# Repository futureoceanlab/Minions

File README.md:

# Minions
This repository contains software and hardware assets for the Minions 
stereo imaging system project. The design and evaluation based on these
assets are thoroughly described in 
<a href="https://www.dropbox.com/s/i847r4oa8v05839/junsuj-ms-2020.pdf?dl=0">Junsu's thesis</a>.

## Circuit
This directory contains the circuit related assets: schematic, board layout 
and the gerber file. They were used to develop and evaluate the necessary
components to communicate and control peripheral electronics of the 
Minion stereo camera components. EAGLE software is required.

## Code
The software components of the project can be broken down into four major
parts:
- **PTV**: We devised a simulation of the settling marine snow. We also 
apply PTV to track those particles and evaluated the performance of the PTV. 
- **Firmware**: Firmware to control cameras and LED during deployment.
- **Optical Simulation**: Simulation tools to evaluate the designs of the stereo
optical system.
- **Optical Analysis**: Analysis of empirical measurements of the imaging 
system and the lighting systems.

More detailed explanations of the code can be found in each of the sub-directories
and in the code itself.

## Mechanical
The mechanical component of the project remains to be done. The assets will
be added as the project progresses.

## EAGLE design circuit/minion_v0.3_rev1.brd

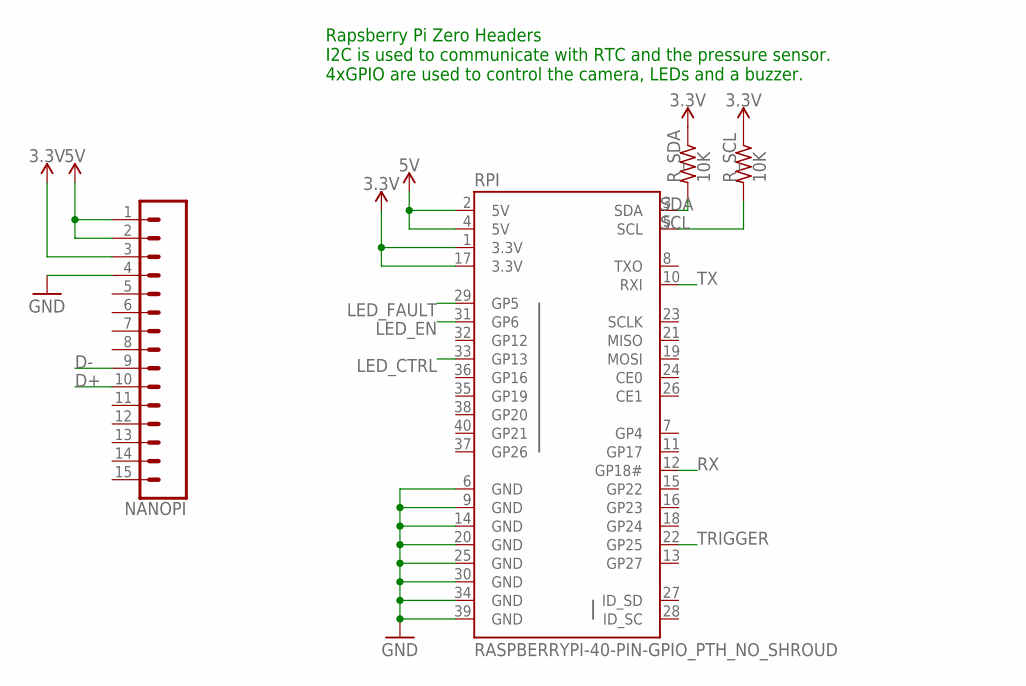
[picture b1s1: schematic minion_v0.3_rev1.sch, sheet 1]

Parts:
NANOPI: CONN_15; 1X15
RPI: RASPBERRYPI-40-PIN-GPIO_PTH_NO_SHROUD; 2X20
R_SCL: 10K; RES_0603
R_SDA: 10K; RES_0603

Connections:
3.3V: NANOPI.3, RPI.1 (3.3V), RPI.17 (3.3V), R_SCL.1, R_SDA.1; also elsewhere on the board
5V: NANOPI.1, NANOPI.2, RPI.2 (5V), RPI.4 (5V); also elsewhere on the board
D+: NANOPI.10; also elsewhere on the board
D-: NANOPI.9; also elsewhere on the board
GND: NANOPI.4, RPI.6 (GND), RPI.9 (GND), RPI.14 (GND), RPI.20 (GND), RPI.25 (GND), RPI.30 (GND), RPI.34 (GND), RPI.39 (GND); also elsewhere on the board
LED_CTRL: RPI.33 (GP13); also elsewhere on the board
LED_EN: RPI.31 (GP6); also elsewhere on the board
LED_FAULT: RPI.29 (GP5); also elsewhere on the board
RX: RPI.12 (GP18#); also elsewhere on the board
SCL: RPI.5 (SCL), R_SCL.2; also elsewhere on the board
SDA: RPI.3 (SDA), R_SDA.2; also elsewhere on the board
TRIGGER: RPI.22 (GP25); also elsewhere on the board
TX: RPI.10 (RXI); also elsewhere on the board

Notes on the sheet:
Rapsberry Pi Zero Headers I2C is used to communicate with RTC and the pressure sensor. 4xGPIO are used to control the camera, LEDs and a buzzer.

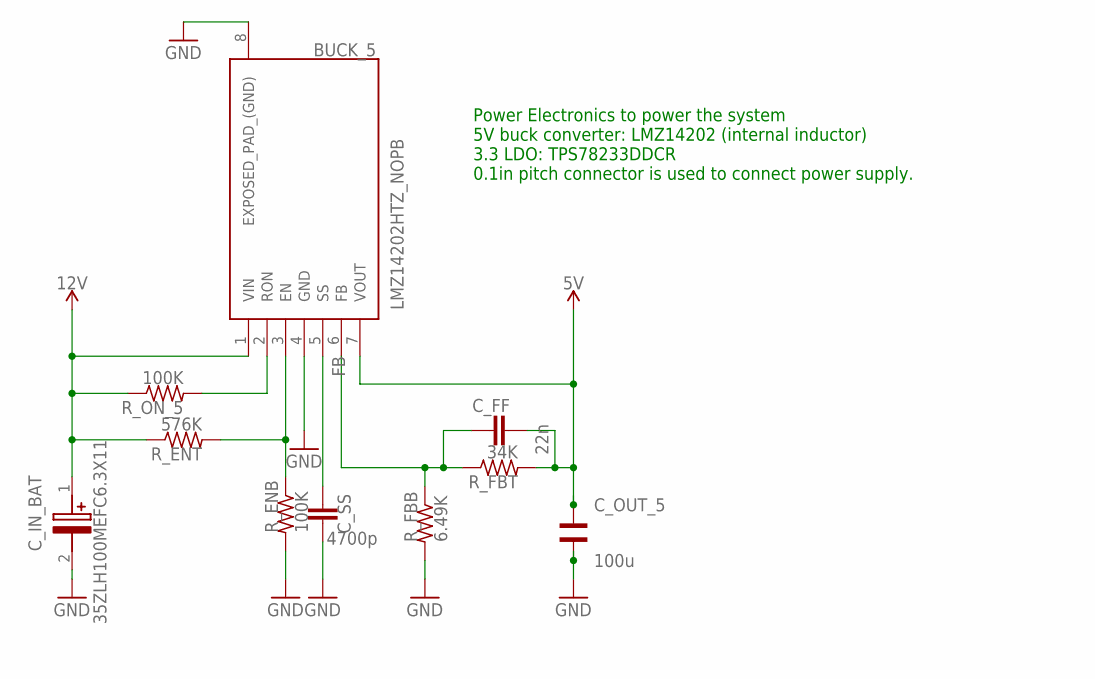
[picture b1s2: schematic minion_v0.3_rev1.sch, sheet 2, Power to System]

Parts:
BUCK_5: LMZ14202HTZ_NOPB; NDW0007A
C_FF: 22n; CAP_0603
C_IN_BAT: 35ZLH100MEFC6.3X11; CAPPRD250W50D680H1250
C_OUT_5: 100u; WCAP-CSGP_1206
C_SS: 4700p; CAP_0603
R_ENB: 100K; RES_0603
R_ENT: 576K; RES_0603
R_FBB: 6.49K; RES_0603
R_FBT: 34K; RES_0603
R_ON_5: 100K; RES_0603

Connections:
5V: BUCK_5.7 (VOUT), C_FF.2, C_OUT_5.2, R_FBT.2; also elsewhere on the board
12V: BUCK_5.1 (VIN), C_IN_BAT.1 (+), R_ENT.1, R_ON_5.1; also elsewhere on the board
FB: BUCK_5.6 (FB), C_FF.1, R_FBB.1, R_FBT.1
GND: BUCK_5.4 (GND), BUCK_5.8 (EXPOSED_PAD_(GND)), C_IN_BAT.2 (-), C_OUT_5.1, C_SS.2, R_ENB.2, R_FBB.2; also elsewhere on the board
unnamed: BUCK_5.2 (RON), R_ON_5.2
unnamed: BUCK_5.3 (EN), R_ENB.1, R_ENT.2
unnamed: BUCK_5.5 (SS), C_SS.1

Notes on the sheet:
Power Electronics to power the system 5V buck converter: LMZ14202 (internal inductor) 3.3 LDO: TPS78233DDCR 0.1in pitch connector is used to connect power supply.

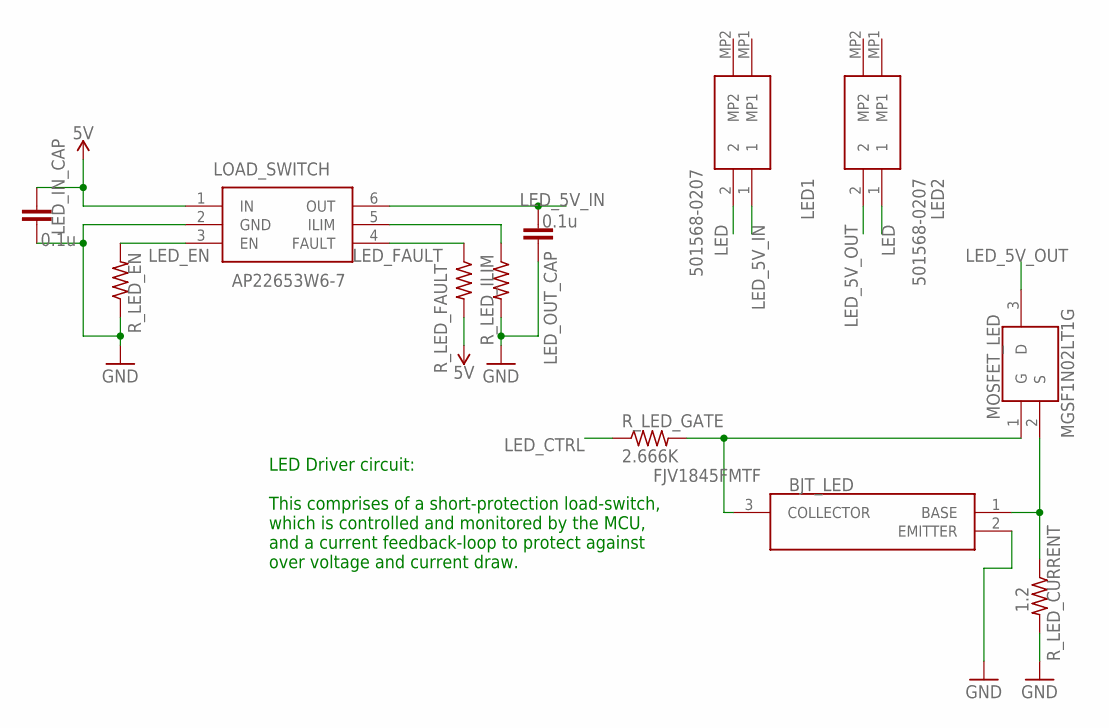
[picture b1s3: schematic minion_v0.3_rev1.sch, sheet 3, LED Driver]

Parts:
BJT_LED: FJV1845FMTF; SOT95P240X114-3N
LED1, LED2: 501568-0207; 5015680207
LED_IN_CAP: 0.1u; CAP_0603
LED_OUT_CAP: 0.1u; CAP_0603
LOAD_SWITCH: AP22653W6-7; SOT95P285X140-6N; MANUFACTURER_PART_NUMBER AP22653; MOUSER_PART_NUMBER 621-AP22653W6-7
MOSFET_LED: MGSF1N02LT1G; SOT96P237X111-3N
R_LED_CURRENT: 1.2; RES_0603
R_LED_EN: 10K; RES_0603
R_LED_FAULT: 10K; RES_0603
R_LED_GATE: 2.666K; RES_0603
R_LED_ILIM: 10K; RES_0603

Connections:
5V: LED_IN_CAP.1, LOAD_SWITCH.1 (IN), R_LED_FAULT.2; also elsewhere on the board
GND: BJT_LED.2 (EMITTER), LED_IN_CAP.2, LED_OUT_CAP.2, LOAD_SWITCH.2 (GND), R_LED_CURRENT.2, R_LED_EN.1, R_LED_ILIM.2; also elsewhere on the board
LED: LED1.2, LED2.1
LED_5V_IN: LED1.1, LED_OUT_CAP.1, LOAD_SWITCH.6 (OUT)
LED_5V_OUT: LED2.2, MOSFET_LED.3 (D)
LED_CTRL: R_LED_GATE.1; also elsewhere on the board
LED_EN: LOAD_SWITCH.3 (EN), R_LED_EN.2; also elsewhere on the board
LED_FAULT: LOAD_SWITCH.4 (FAULT), R_LED_FAULT.1; also elsewhere on the board
unnamed: BJT_LED.3 (COLLECTOR), MOSFET_LED.1 (G), R_LED_GATE.2
unnamed: BJT_LED.1 (BASE), MOSFET_LED.2 (S), R_LED_CURRENT.1
unnamed: LOAD_SWITCH.5 (ILIM), R_LED_ILIM.1

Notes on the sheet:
LED Driver circuit: This comprises of a short-protection load-switch, which is controlled and monitored by the MCU, and a current feedback-loop to protect against over voltage and current draw.

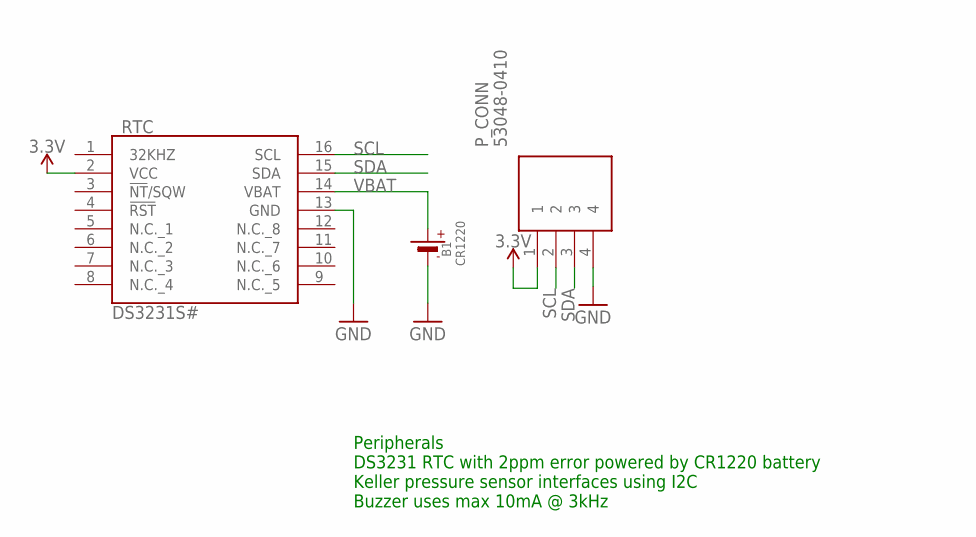
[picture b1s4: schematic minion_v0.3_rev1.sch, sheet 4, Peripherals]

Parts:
B1: CR1220
P_CONN: 53048-0410; SHDR4W35P0X125_1X4_675X550X370
RTC: DS3231S#; SOIC127P1032X265-16N

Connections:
3.3V: P_CONN.1, RTC.2 (VCC); also elsewhere on the board
GND: B1.-, P_CONN.4, RTC.13 (GND); also elsewhere on the board
SCL: P_CONN.2, RTC.16 (SCL); also elsewhere on the board
SDA: P_CONN.3, RTC.15 (SDA); also elsewhere on the board
VBAT: B1.+$1 (+), RTC.14 (VBAT)

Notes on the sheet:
Peripherals DS3231 RTC with 2ppm error powered by CR1220 battery Keller pressure sensor interfaces using I2C Buzzer uses max 10mA @ 3kHz

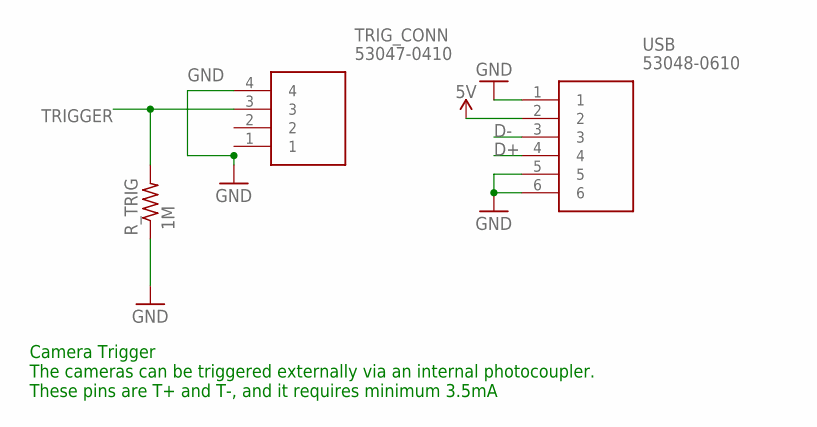
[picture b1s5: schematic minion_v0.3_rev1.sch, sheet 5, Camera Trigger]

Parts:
R_TRIG: 1M; RES_0603
TRIG_CONN: 53047-0410
USB: 53048-0610; SHDR6W35P0X125_1X6_925X550X370

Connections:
5V: USB.2; also elsewhere on the board
D+: USB.4; also elsewhere on the board
D-: USB.3; also elsewhere on the board
GND: R_TRIG.1, TRIG_CONN.1, TRIG_CONN.4, USB.1, USB.5, USB.6; also elsewhere on the board
TRIGGER: R_TRIG.2, TRIG_CONN.3; also elsewhere on the board

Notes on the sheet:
Camera Trigger The cameras can be triggered externally via an internal photocoupler. These pins are T+ and T-, and it requires minimum 3.5mA

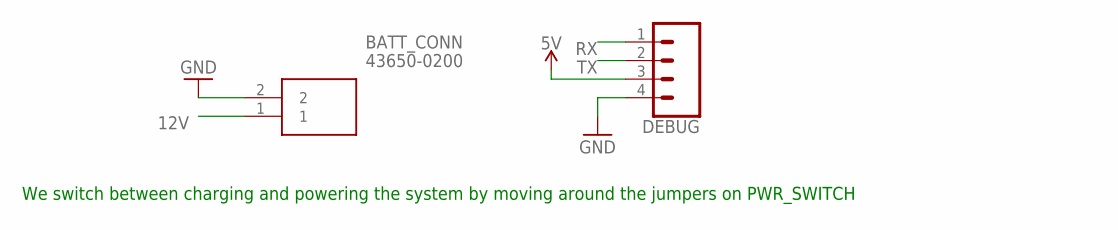
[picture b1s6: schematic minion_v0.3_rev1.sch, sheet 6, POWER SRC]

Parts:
BATT_CONN: 43650-0200
DEBUG: CONN_04; 1X04

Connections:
5V: DEBUG.3; also elsewhere on the board
12V: BATT_CONN.1; also elsewhere on the board
GND: BATT_CONN.2, DEBUG.4; also elsewhere on the board
RX: DEBUG.1; also elsewhere on the board
TX: DEBUG.2; also elsewhere on the board

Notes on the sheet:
We switch between charging and powering the system by moving around the jumpers on PWR_SWITCH

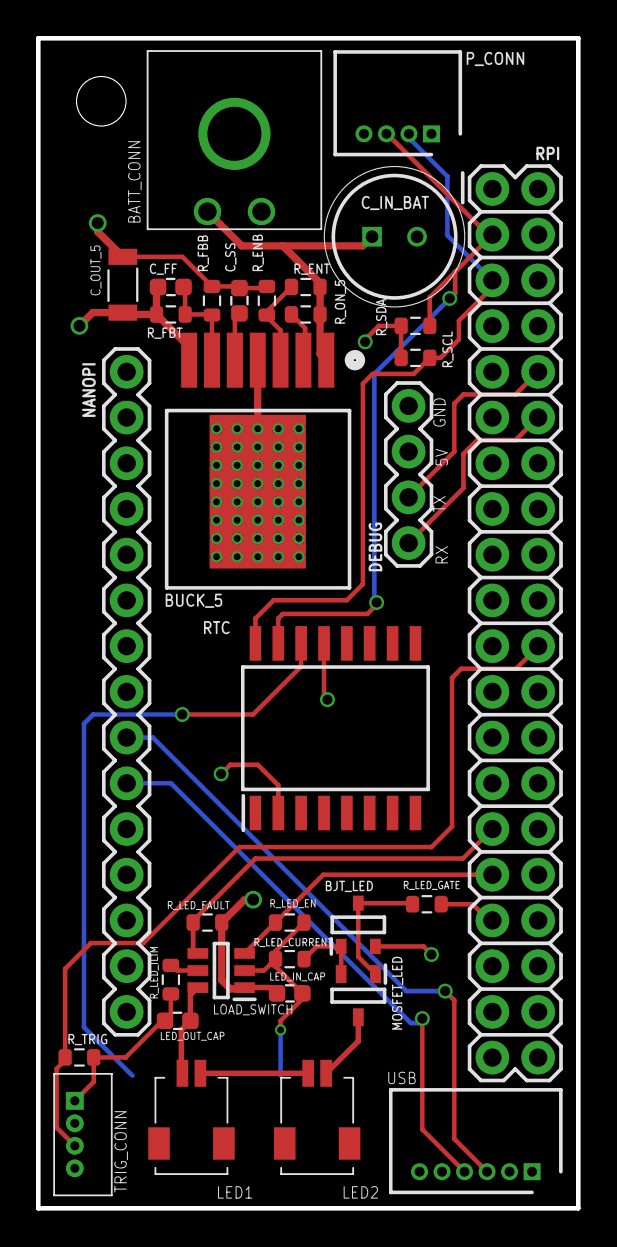
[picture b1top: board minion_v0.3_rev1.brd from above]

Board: 4 copper layers, 30.0 x 65.0 mm, 34 parts (1 on the bottom side), 25 nets.

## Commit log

2020-06-07 remove old commit
2020-06-07 add code
2020-08-10 add schematic, board and gereber
2020-08-10 version of handling multiple clients with potential failed connection
2020-08-18 move firmware code into one directory
2020-08-18 remove top minions- firmware code
2020-08-18 move calibration to optical analysis
2020-08-18 move single camera focus (contrast measure) under otpical-analysis
2020-08-18 add led and camera resolution analysis
2020-08-18 update the README
2020-08-18 edit code block
2020-08-18 modify README and add more comments on the main.cpp
2020-08-18 add comments to individual functions and scripts
2020-08-18 change to air from edmund in water analysis
2020-08-18 add readme
2020-08-18 add comments and readme
2020-08-19 Add Readme as an introduction to this set of codes
2020-08-19 add high level readme
2020-08-19 add initial code for simulations
2020-08-19 ignore image files in simulations
2020-08-19 high-level editing of the readme
2020-08-19 add a little more detail on the software
2020-08-19 add comments and clean up codes
2020-08-19 move the clean blur empirical measurement to the analysis directory
2020-08-19 add the blur
2020-08-19 Remove vertical motion related
2020-08-19 clean up refractive index code
2020-08-19 clean up overlap vol
2020-08-19 add readme and comments to the main code
2020-08-19 remove the images
2020-08-19 remove esd_detectability images
2020-08-20 clean up the code and add readme
2020-08-22 move the old version of the camera firmware
2020-08-22 update with the latest camera firmware for fail-safe / multi-operation
2020-08-22 add a signal between the camera and imaging firmware. Requires test
2020-08-23 format the imaging firmware with further input arguments and signal handling
2020-08-23 modify bash to meet the new argument requirements for imaging firmware as well as to provide PID for control in the main camera
2020-08-23 added input argument flags, but sync timer seems no longer necessary
2020-08-24 convert functions to camel case
2020-08-24 add logging of time skews and server seconds as well as change the funtion names to came case
2020-08-24 check directory exists for camera firmware
2020-08-24 Add back the synchronization timer necessary for re-synchronization
2020-08-25 synchronization: simplify the skew code; the rest: add header comments in include files
2020-08-25 fix format error
2020-08-27 add laser cutting parts
2020-08-27 move the lasert cutting parts under the same directory
2020-08-27 add README.md
2020-08-29 add input arguments for user control
2020-09-14 add single camera mount and move the underwater camera mount side joints
2020-09-14 add the underwater housing mount and chassis
2020-09-25 add instructions manual for setting up and testing the optical elements

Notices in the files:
parts and their libraries:
microbuilder: This work is placed in the public domain, and may be freely used for commercial and non-commercial work with the following conditions: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
Wurth_Elektronik_Passive_Capacitors_rev1: Copyright: Würth Elektronik
